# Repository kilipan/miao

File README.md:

# MIAO (喵) ch552t MCU board

### Changelog
2023-09-29 initial commit  
2023-09-30 fixed pinout to correspond to Xiao, added jumper to choose between RX/CS on pin 8, completely rerouted

| :zap: The hardware design is tested and confirmed working as of the latest commit. Nevertheless I cannot guarantee anything. **Use at your own risk!** |
|---|

## About
MIAO is a cheap drop-in replacement for the Seeeduino Xiao series.

喵 is the Hanzi for "miāo", which is Mandarin for "meow".

The board is available in two variants:
- A super cheap, hand-solderable version in `hw_handsolder` (since castellated holes are expensive, this version doesn't support them.)
- A cheap, pcba version in `hw_pcba`, featuring castellated holes

## Pictures
Renders of the handsolderable version and a screenshot of the schematic can be unfolded below.

<details>
<summary> Front view render </summary>

</details>
<details>
<summary> Back view render </summary>

</details>
<details>
<summary> Schematic </summary>

</details>

# Features
MIAO features:
- Utilizes wch's ch552t microcontroller, which at the time of writing costs a few dozen cents! 
- SPI and UART pins in the same places as Xiao (use jumper to choose between RX/CS on pin 8)
- 2 Analogue pins
- 4 additional broken out pins (not pads!) compared to the Xiao boards:
  - 2 free GPIOs
  - reset pin (pull HIGH for reset)
  - boot pin (pull HIGH for entering bootloader)
- Full ESD protection incl. protection against reverse current and overcurrent
- Top-mount USB port for maximum drop-in-ability
- Optional power or user led (on the backside for the handsolderable version; bridge left and middle part of jumper for always-on, middle and right for user controllable via P3.3)
- Optional reset and bootloader buttons (on the backside for the handsolderable version)
- Optional footprint for connecting USB Shield to GND in a way that fits your application
- Cute pixel cat on the back! 🐱

# Availability
As production files are open sourced, you can get these manufactured at your favorite PCB-manufacturer. Alternatively, [keeb.supply](https://keeb.supply/) is selling the PCBA version usage-ready for a great price! Thanks guys! <3
Non-affiliate link: [Miao page on keeb.supply](https://keeb.supply/products/miao)

# BOM (handsolder only)
**This BOM is for the handsolderable version only.** For the PCBA version please refer to the given files.

| Amount | Part | LCSC part number | Silkscreen Reference | Comment |
|-------:|:-----|:-----------------|:---------------------|:--------|
|      1 | ch552t microcontroller | [C111367](https://www.lcsc.com/product-detail/USB-ICs_WCH-Jiangsu-Qin-Heng-CH552T_C111367.html) | U1 | |
|      1 | top-mount USB-C receptacle | [C2765186](https://www.lcsc.com/product-detail/_SHOU-HAN-_C2765186.html) | [none] | |
|      1 | SOT-23 ESD protection diode | [C6807798](https://www.lcsc.com/product-detail/_FUXINSEMI-_C6807798.html) | U2 | |
|      1 | SOD-323 Schottky diode | [C193668](https://www.lcsc.com/product-detail/_Nexperia-_C193668.html) | D2 | |
|      1 | 0603 Fuse | [C311055](https://www.lcsc.com/product-detail/_AEM-_C311055.html) | F1 | |
|      1 | 0603 10kΩ Resistor | [C25804](https://www.lcsc.com/product-detail/_UNI-ROYAL-Uniroyal-Elec-_C25804.html) | R1 | |
|      2 | 0603 5.1kΩ Resistor | [C23186](https://www.lcsc.com/product-detail/_UNI-ROYAL-Uniroyal-Elec-_C23186.html) | R4, R5 | |
|      2 | 0603 100nF Capacitors | [C384773](https://www.lcsc.com/product-detail/Multilayer-Ceramic-Capacitors-MLCC-SMD-SMT_Walsin-Tech-Corp-0603X334K100CT_C384773.html) | C1, C2 | Take care, these need to be soldered in vertically, as indicated by the small dashes on the silkscreen! |
|    [1] | [optional] 1kΩ Resistor | [C21190](https://www.lcsc.com/product-detail/_UNI-ROYAL-Uniroyal-Elec-_C21190.html) | R2 | on the backside |
|    [2] | [optional] push buttons | [C115357](https://www.lcsc.com/product-detail/_ALPSALPINE-_C115357.html) | B, R | on the backside |
|    [1] | [optional] LED | [C434442](https://www.lcsc.com/product-detail/_Yongyu-Photoelectric-_C434442.html) | D1 | on the backside |

# Firmware
The project is inspired by and designed for usage with
[semickolon](https://github.com/semickolon/)'s
[FAK firmware](https://github.com/semickolon/fak/), but it's obviously not
limited to that! Refer to the ch552t documentation and the many other ch55x
projects for more details.

# License
The hardware design is licensed under the CERN-OHL-v2-S license, so feel free
to look at the sources and remix to your heart's content! :)

# Thanks
- semickolon for creating FAK, inspiring the project and helping with design considerations
- 0xCB for open-sourcing the [Helios](https://github.com/0xCB-dev/0xCB-Helios/) and providing inspiration for the ESD stuff
- the Clacktales community for their continued support, discussion, and interest in the project
- Pete Johanson for noticing and pointing out the pinout mix-up in the initially commited version

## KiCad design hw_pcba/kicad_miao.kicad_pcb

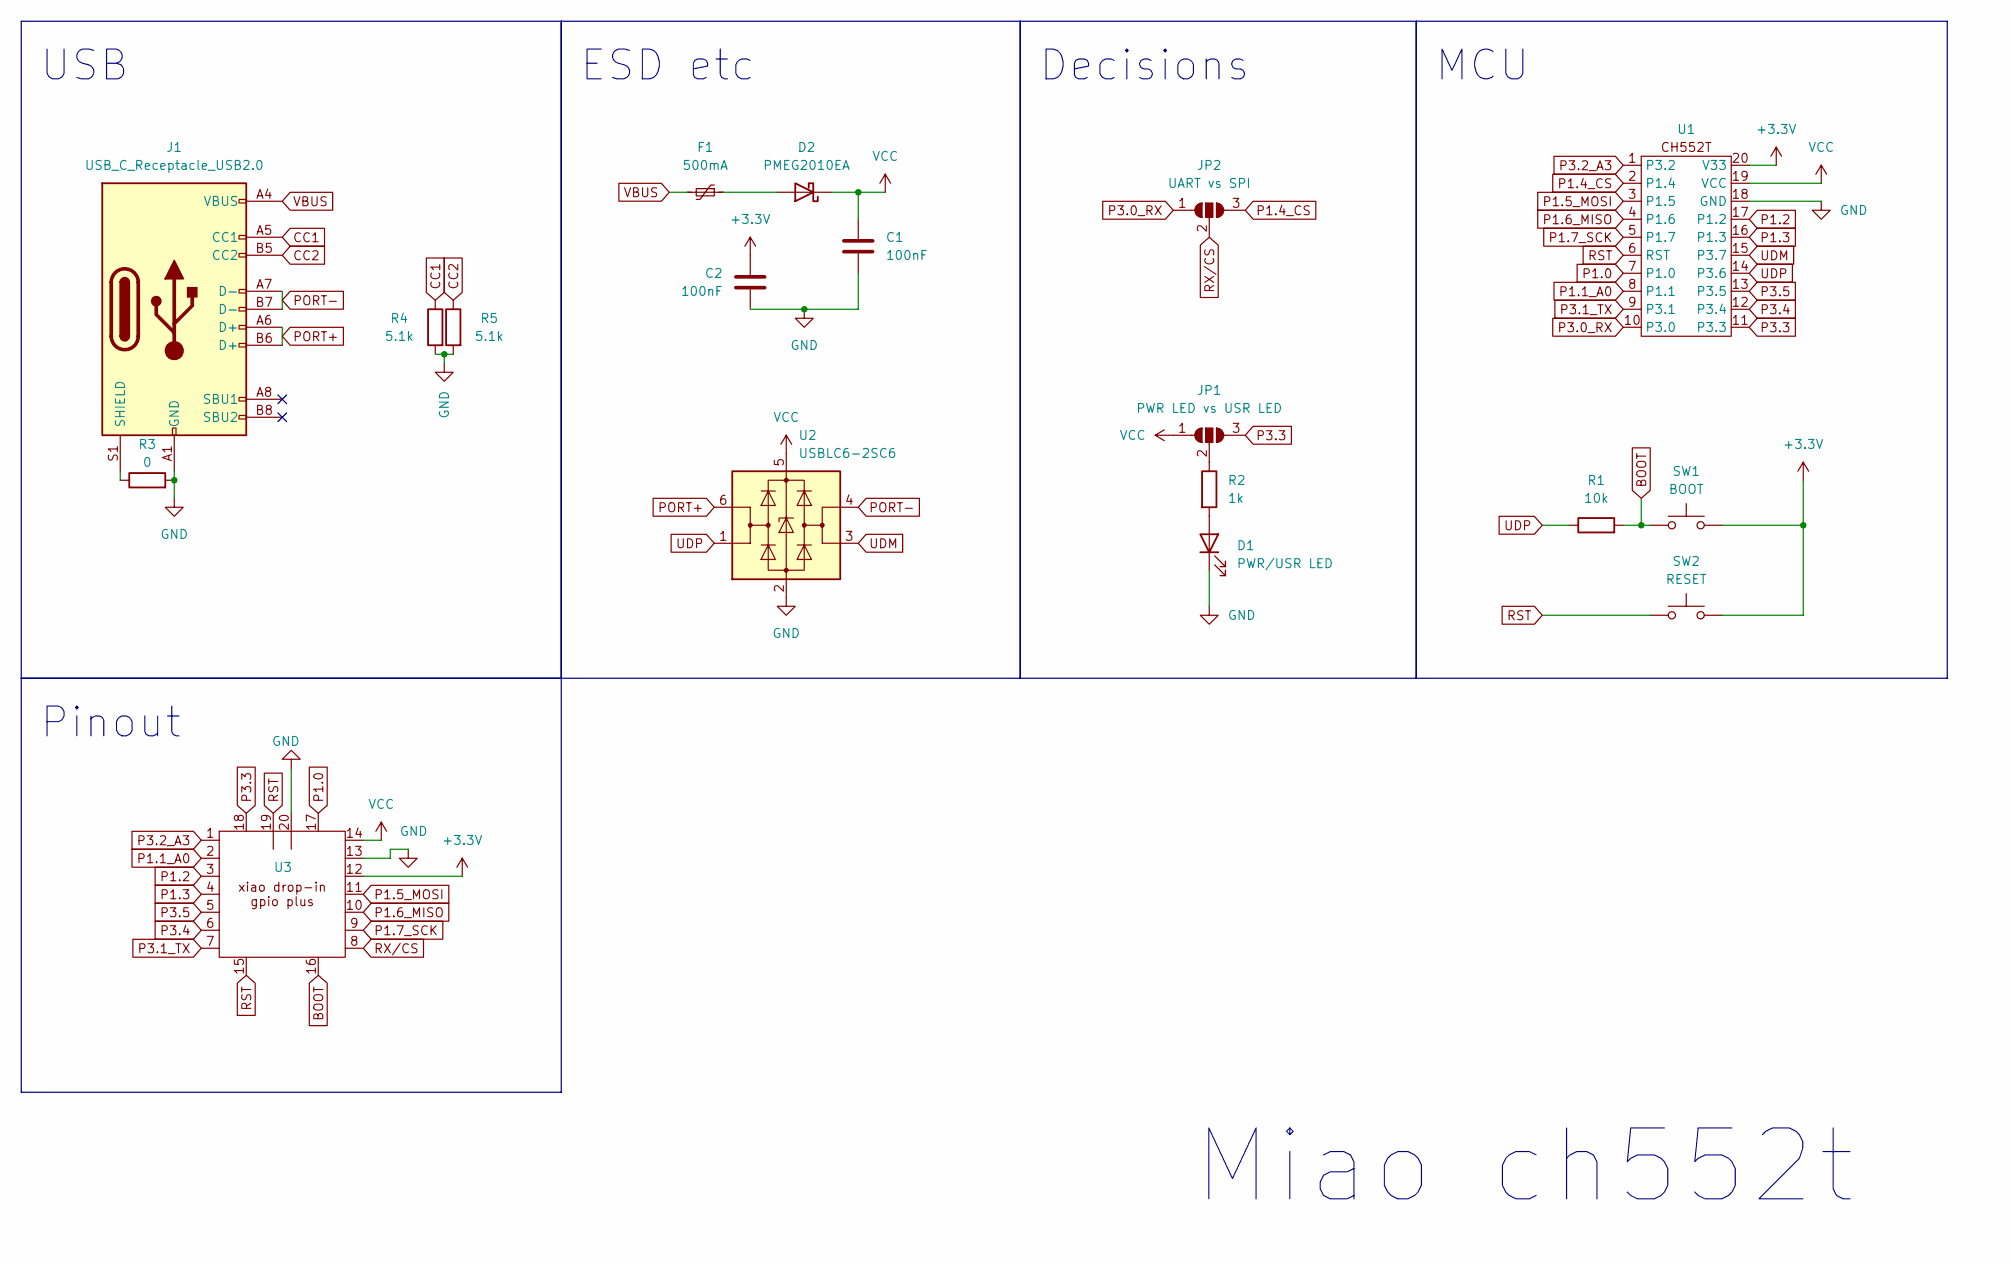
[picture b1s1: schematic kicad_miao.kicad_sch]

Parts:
C1, C2: 100nF; C_0402_1005Metric; LCSC C1525
D1: PWR/USR LED; LED_0402_1005Metric; LCSC C130724
D2: PMEG2010EA; D_0402_1005Metric; LCSC C2837790
F1: 500mA; Fuse_0402_1005Metric; LCSC C210357
J1: USB_C_Receptacle_USB2.0; USB_C_Receptacle_HRO_TYPE-C-31-M-12; JLCPCB_CORRECTION 0; -1.35; 0
JP1: PWR LED vs USR LED; SolderJumper-3_P1.3mm_Open_RoundedPad1.0x1.5mm_NumberLabels
JP2: UART vs SPI; SolderJumper-3_P1.3mm_Open_RoundedPad1.0x1.5mm_NumberLabels
R1: 10k; R_0402_1005Metric; LCSC C25744
R2: 1k; R_0402_1005Metric; LCSC C11702
R3: 0; R_0402_1005Metric; LCSC C17168
R4, R5: 5.1k; R_0402_1005Metric; LCSC C25905
SW1: BOOT; SW_Push_SPST_NO_Alps_SKRK; LCSC C115357
SW2: RESET; SW_Push_SPST_NO_Alps_SKRK; LCSC C115357
U1: TSSOP-20_4.4x6.5mm_P0.65mm; JLCPCB_CORRECTION 0; 0; 270
U2: USBLC6-2SC6; SOT-23-6; JLCPCB_CORRECTION 0; 0; 270
U3: xiao_drop-in_gpio_usb_no_cutout; xiao_drop-in_gpio_plus_4_castellated

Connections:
+3.3V: C2.1, SW1.2, SW2.2, U1.20 (V33), U3.12
BOOT: R1.2, SW1.1, U3.16
CC1: J1.A5 (CC1), R4.1
CC2: J1.B5 (CC2), R5.1
GND: C1.2, C2.2, D1.1 (K), J1.A1 (GND), J1.A12 (GND), J1.B1 (GND), J1.B12 (GND), R3.2, R4.2, R5.2, U1.18 (GND), U2.2 (GND), U3.13, U3.20
unnamed: D1.2 (A), R2.2
unnamed: D2.2 (A), F1.1
unnamed: J1.S1 (SHIELD), R3.1
unnamed: JP1.2 (C), R2.1
P1.0: U1.7 (P1.0), U3.17
P1.1_A0: U1.8 (P1.1), U3.2
P1.2: U1.17 (P1.2), U3.3
P1.3: U1.16 (P1.3), U3.4
P1.4_CS: JP2.3 (B), U1.2 (P1.4)
P1.5_MOSI: U1.3 (P1.5), U3.11
P1.6_MISO: U1.4 (P1.6), U3.10
P1.7_SCK: U1.5 (P1.7), U3.9
P3.0_RX: JP2.1 (A), U1.10 (P3.0)
P3.1_TX: U1.9 (P3.1), U3.7
P3.2_A3: U1.1 (P3.2), U3.1
P3.3: JP1.3 (B), U1.11 (P3.3), U3.18
P3.4: U1.12 (P3.4), U3.6
P3.5: U1.13 (P3.5), U3.5
PORT+: J1.A6 (D+), J1.B6 (D+), U2.6 (I/O1)
PORT-: J1.A7 (D-), J1.B7 (D-), U2.4 (I/O2)
RST: SW2.1, U1.6 (RST), U3.15, U3.19
RX/CS: JP2.2 (C), U3.8
UDM: U1.15 (P3.7), U2.3 (I/O2)
UDP: R1.1, U1.14 (P3.6), U2.1 (I/O1)
VBUS: F1.2, J1.A4 (VBUS), J1.A9 (VBUS), J1.B4 (VBUS), J1.B9 (VBUS)
VCC: C1.1, D2.1 (K), JP1.1 (A), U1.19 (VCC), U2.5 (VBUS), U3.14

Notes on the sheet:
MCU
Miao ch552t
USB
Decisions
ESD etc
Pinout

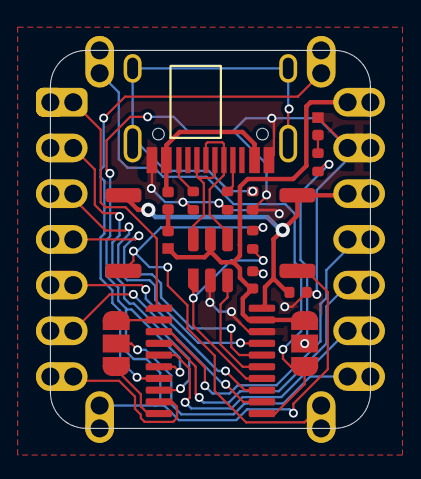
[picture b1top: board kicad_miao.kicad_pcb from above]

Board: 2 copper layers, 17.8 x 21.0 mm, 18 parts (0 on the bottom side), 31 nets.

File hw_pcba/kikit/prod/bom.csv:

Comment,Designator,Footprint,LCSC
5.1k,"R4,R5",Resistor_SMD:R_0402_1005Metric,C25905
1k,R2,Resistor_SMD:R_0402_1005Metric,C11702
~,U1,Package_SO:TSSOP-20_4.4x6.5mm_P0.65mm,C111367
PWR/USR LED,D1,LED_SMD:LED_0402_1005Metric,C130724
RESET,SW2,Button_Switch_SMD:SW_Push_SPST_NO_Alps_SKRK,C115357
10k,R1,Resistor_SMD:R_0402_1005Metric,C25744
PMEG2010EA,D2,Diode_SMD:D_0402_1005Metric,C2837790
BOOT,SW1,Button_Switch_SMD:SW_Push_SPST_NO_Alps_SKRK,C115357
100nF,"C1,C2",Capacitor_SMD:C_0402_1005Metric,C1525
0,R3,Resistor_SMD:R_0402_1005Metric,C17168
USBLC6-2SC6,U2,Package_TO_SOT_SMD:SOT-23-6,C2687116
USB_C_Receptacle_USB2.0,J1,Connector_USB:USB_C_Receptacle_HRO_TYPE-C-31-M-12,C2765186
500mA,F1,Fuse:Fuse_0402_1005Metric,C210357

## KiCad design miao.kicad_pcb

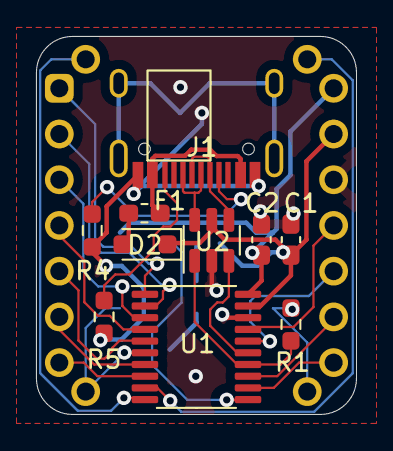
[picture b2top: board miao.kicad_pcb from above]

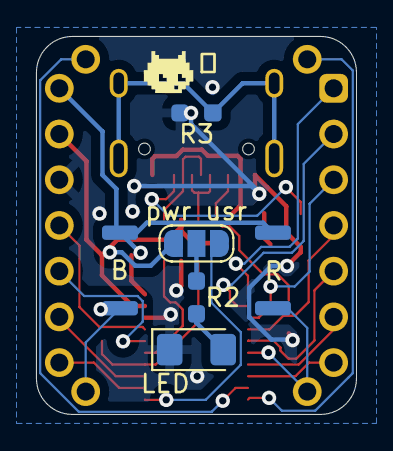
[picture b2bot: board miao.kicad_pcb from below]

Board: 2 copper layers, 17.8 x 21.0 mm, 17 parts (6 on the bottom side), 30 nets.

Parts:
B: BOOT; SW_Push_SPST_NO_Alps_SKRK
C1, C2: 100nF; C_0603_1608Metric_Pad1.08x0.95mm_HandSolder
D2: PMEG2010BELD; D_SOD-323_HandSoldering
F1: 500mA; Fuse_0603_1608Metric_Pad1.05x0.95mm_HandSolder
J1: USB_C_Receptacle_USB2.0; USB_C_Receptacle_HRO_TYPE-C-31-M-12
JP1: SolderJumper_3_Open; SolderJumper-3_P1.3mm_Open_RoundedPad1.0x1.5mm_NumberLabels
LED: PWR/USR LED; LED_1206_3216Metric_Pad1.42x1.75mm_HandSolder
R: RESET; SW_Push_SPST_NO_Alps_SKRK
R1: 10k; R_0603_1608Metric_Pad0.98x0.95mm_HandSolder
R2: 1k; R_0603_1608Metric_Pad0.98x0.95mm_HandSolder
R3: 0; R_0603_1608Metric_Pad0.98x0.95mm_HandSolder
R4, R5: 5.1k; R_0603_1608Metric_Pad0.98x0.95mm_HandSolder
U1: TSSOP-20_4.4x6.5mm_P0.65mm
U2: USBLC6-2SC6; SOT-23-6
U3: xiao_drop-in_gpio_usb_no_cutout; apfel_xiao_drop-in_gpio_plus_4

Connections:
+3.3V: B.2, C2.1, R.2, U1.20 (V33), U3.14
BOOT: B.1, R1.2, U3.16
CC1: J1.A5 (CC1), R4.1
CC2: J1.B5 (CC2), R5.1
GND: C1.2, C2.2, J1.A1 (GND), J1.A12 (GND), J1.B1 (GND), J1.B12 (GND), LED.1 (K), R3.2, R4.2, R5.2, U1.18 (GND), U2.2 (GND), U3.12
unnamed: LED.2 (A), R2.2
unnamed: D2.2 (A), F1.1
unnamed: J1.S1 (SHIELD), R3.1
unnamed: JP1.2 (C), R2.1
P1.0: U1.7 (P1.0), U3.6
P1.1: U1.8 (P1.1), U3.7
P1.2: U1.17 (P1.2), U3.11
P1.3: U1.16 (P1.3), U3.10
P1.4: U1.2 (P1.4), U3.2
P1.5: U1.3 (P1.5), U3.3
P1.6: U1.4 (P1.6), U3.4
P1.7: U1.5 (P1.7), U3.5
P3.0: U1.10 (P3.0), U3.18
P3.1: U1.9 (P3.1), U3.17
P3.2: U1.1 (P3.2), U3.1
P3.3: JP1.3 (B), U1.11 (P3.3)
P3.4: U1.12 (P3.4), U3.8
P3.5: U1.13 (P3.5), U3.9
PORT+: J1.A6 (D+), J1.B6 (D+), U2.6 (I/O1)
PORT-: J1.A7 (D-), J1.B7 (D-), U2.4 (I/O2)
RST: R.1, U1.6 (RST), U3.15
UDM: U1.15 (P3.7), U2.3 (I/O2)
UDP: R1.1, U1.14 (P3.6), U2.1 (I/O1)
VBUS: F1.2, J1.A4 (VBUS), J1.A9 (VBUS), J1.B4 (VBUS), J1.B9 (VBUS)
VCC: C1.1, D2.1 (K), JP1.1 (A), U1.19 (VCC), U2.5 (VBUS), U3.13

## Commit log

2023-09-28 add renders
2023-09-28 remove erroneously pushed lck fie
2023-09-28 add kicad runtime files to gitignore
2023-09-28 rename zipped production files to include miao
2023-09-30 hopefully fix pin-out errors to add more compat
2023-10-01 update README, clean-up schematic
2023-10-01 add folds to README
2023-10-01 update production files
2023-11-20 Add BOM, change t
2023-11-20 Add silkscreen references and comments to BOM
2024-01-03 update with pcba version, reflect in readme
2024-01-03 fix typo
2024-01-05 add kicad symbol and footprint
2024-01-05 add 3d files
2024-02-22 clean up
